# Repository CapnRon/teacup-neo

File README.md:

# Teacup Neo

T41 (QFN96) adaptation of the [Teacup Rev-C](https://github.com/CapnRon/Teacup) T31 development board.

Targets **T41NQ (128MB)**, **T41XQ (256MB)**, and **T41LQ (64MB)** — all three are
pin-identical in the QFN96 package, so one layout serves all three as a stuffing
option (LQ needs the DDR rail set to 1.8V instead of 1.35V via the FB divider).

> **Where this is going:** teacup-neo is the single-SoC (T41) proof for a modular
> platform — a universal baseboard + per-SoC MXM3 interposer modules that host any
> Ingenic T-series/A1 SoC regardless of package. Full spec in
> [`docs/UNIVERSAL.md`](docs/UNIVERSAL.md).

## Status

| Stage | State |
|-------|-------|
| Pin map / power design | complete, verified against 3 datasheets |
| QFN96 footprint + T41NQ symbol | KiCad-validated |
| Schematic | **netlist-verified** — all 97 SoC pins on intended nets, 0 peripheral connections lost |
| PCB netlist applied | 479 pads re-netted, 0 mismatch |
| Routing | **~83% auto-routed** (FreeRouting); 78 nets + placement + 3 shorts need GUI finishing |
| Manufacturing outputs | BOM/pos complete; Gerbers are a **draft** (board not yet fab-ready) |

**This board is NOT fab-ready.** The design (schematic + netlist) is complete and
fully verified, but the PCB was auto-routed headlessly with best-effort blind
placement. Before fabrication it needs, in the KiCad GUI:
- placement de-overlap of the bottom-side power section (7 courtyard overlaps)
- the 78 remaining ratsnest connections routed
- 3 shorts / clearance violations resolved
- **MIPI CSI routed as 100 ohm impedance-controlled differential pairs** (an
  autorouter does not do controlled impedance)
- SFC/DDR length + return-path review per the T41 Hardware Design Guide

## Power tree

2x SY8089A1AAC buck (core 0.8V/2A EN<-1.35V, DDR 1.35V EN<-1.8V) + kept AZ1117
LDOs (3.3V, 1.8V). EN cascade gives the datasheet power-on order. See `docs/POWER.md`.

## Layout

- `hw/` — KiCad project (based on TeaCup(C)3.3)
- `hw/Manufacturing/` — draft Gerbers, drill, BOM, position, DRC report
- `docs/` — pin maps, power design, netlist verification
- `scripts/` — the headless generators (footprint, symbol, schematic, PCB, routing)
- `reference/` — upstream 3.3 artifacts

Built headlessly with KiCad 9.0.2 (kicad-cli + pcbnew) + FreeRouting 1.9.0.

License: GPL-3.0 (inherited from upstream).

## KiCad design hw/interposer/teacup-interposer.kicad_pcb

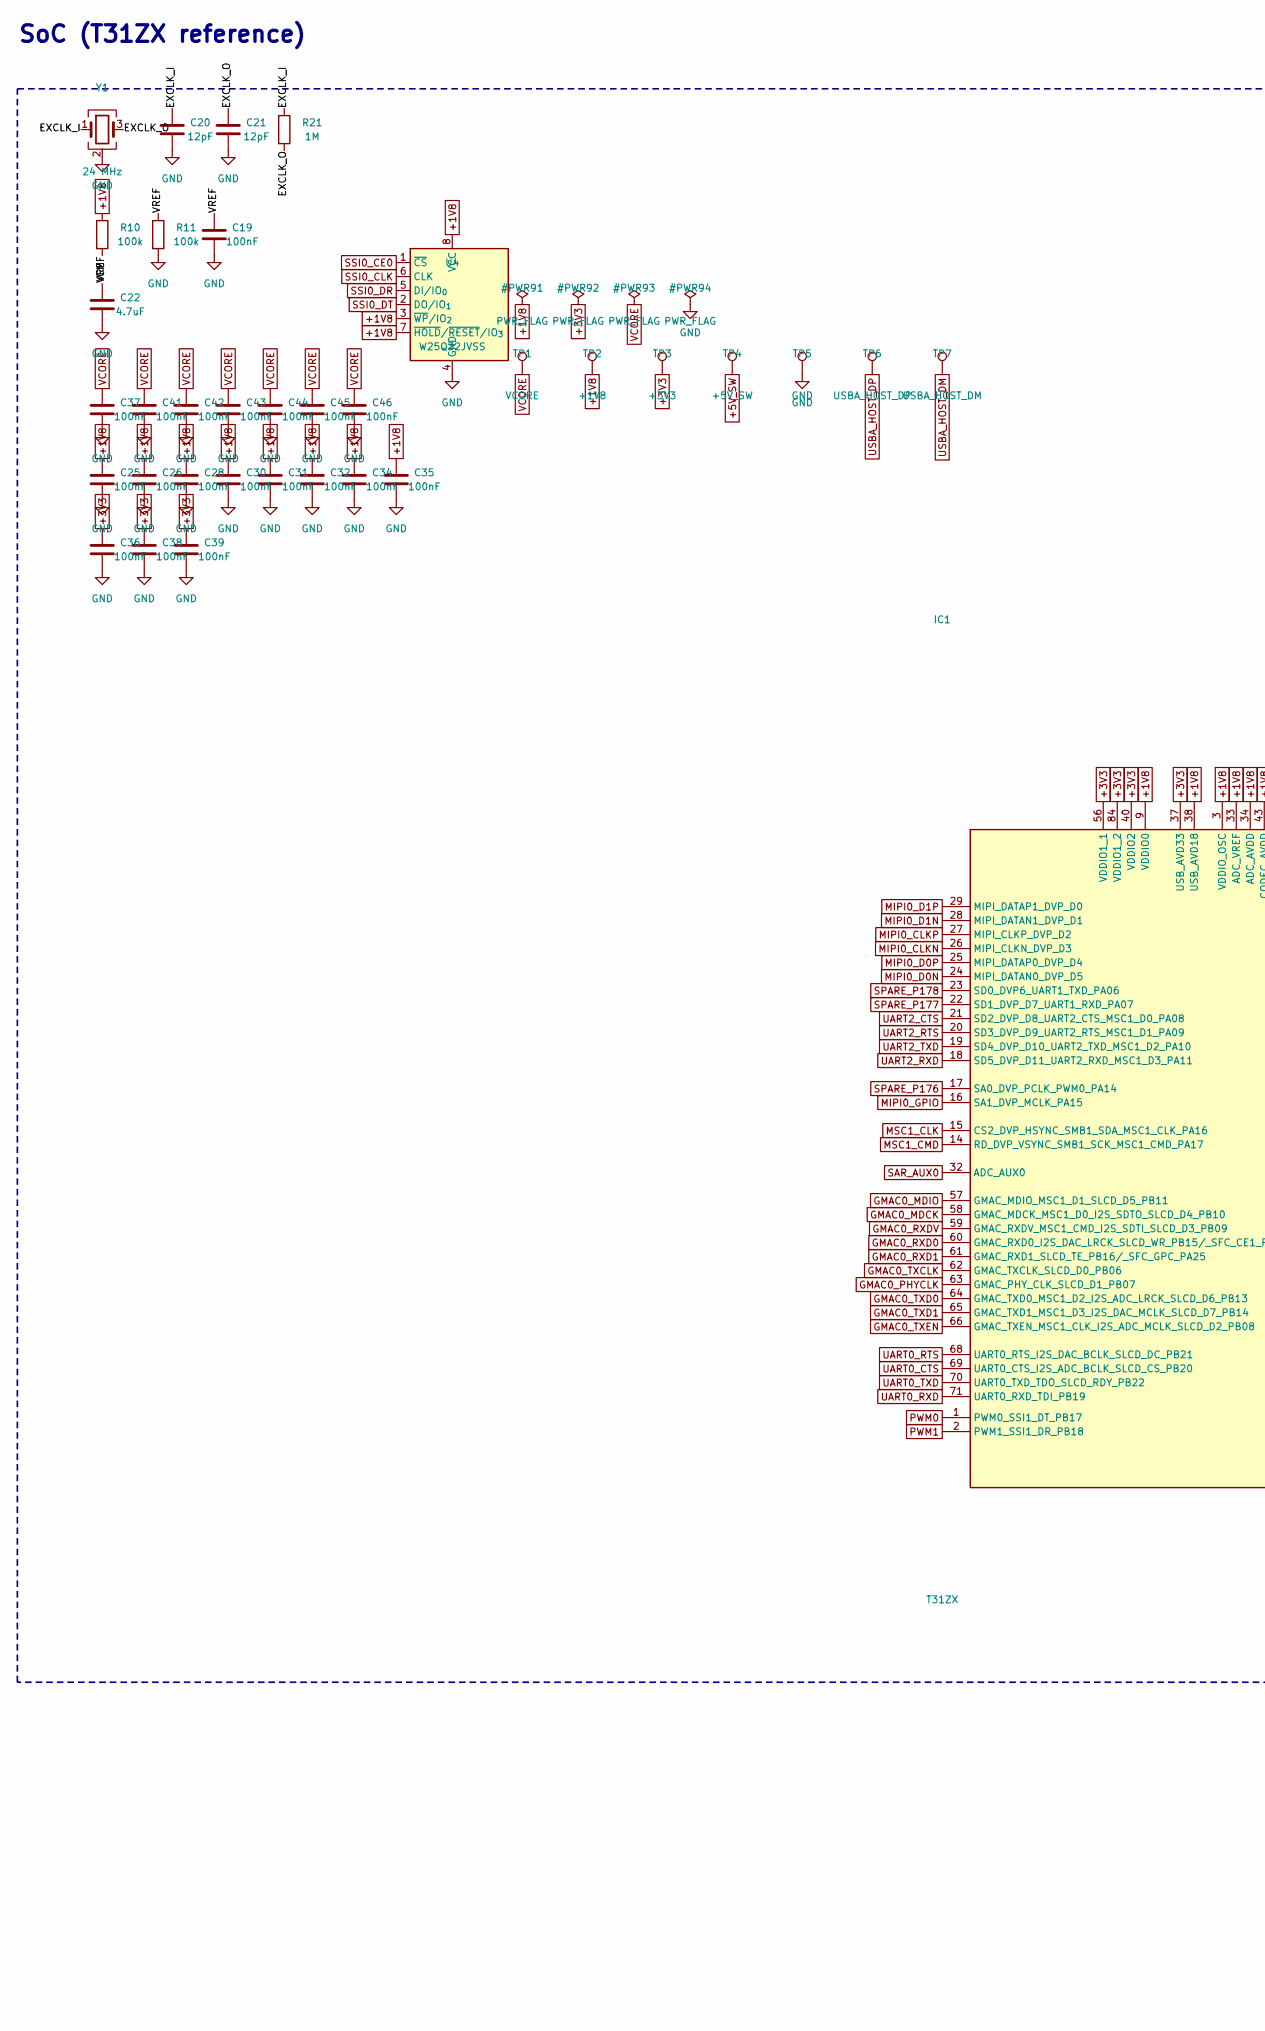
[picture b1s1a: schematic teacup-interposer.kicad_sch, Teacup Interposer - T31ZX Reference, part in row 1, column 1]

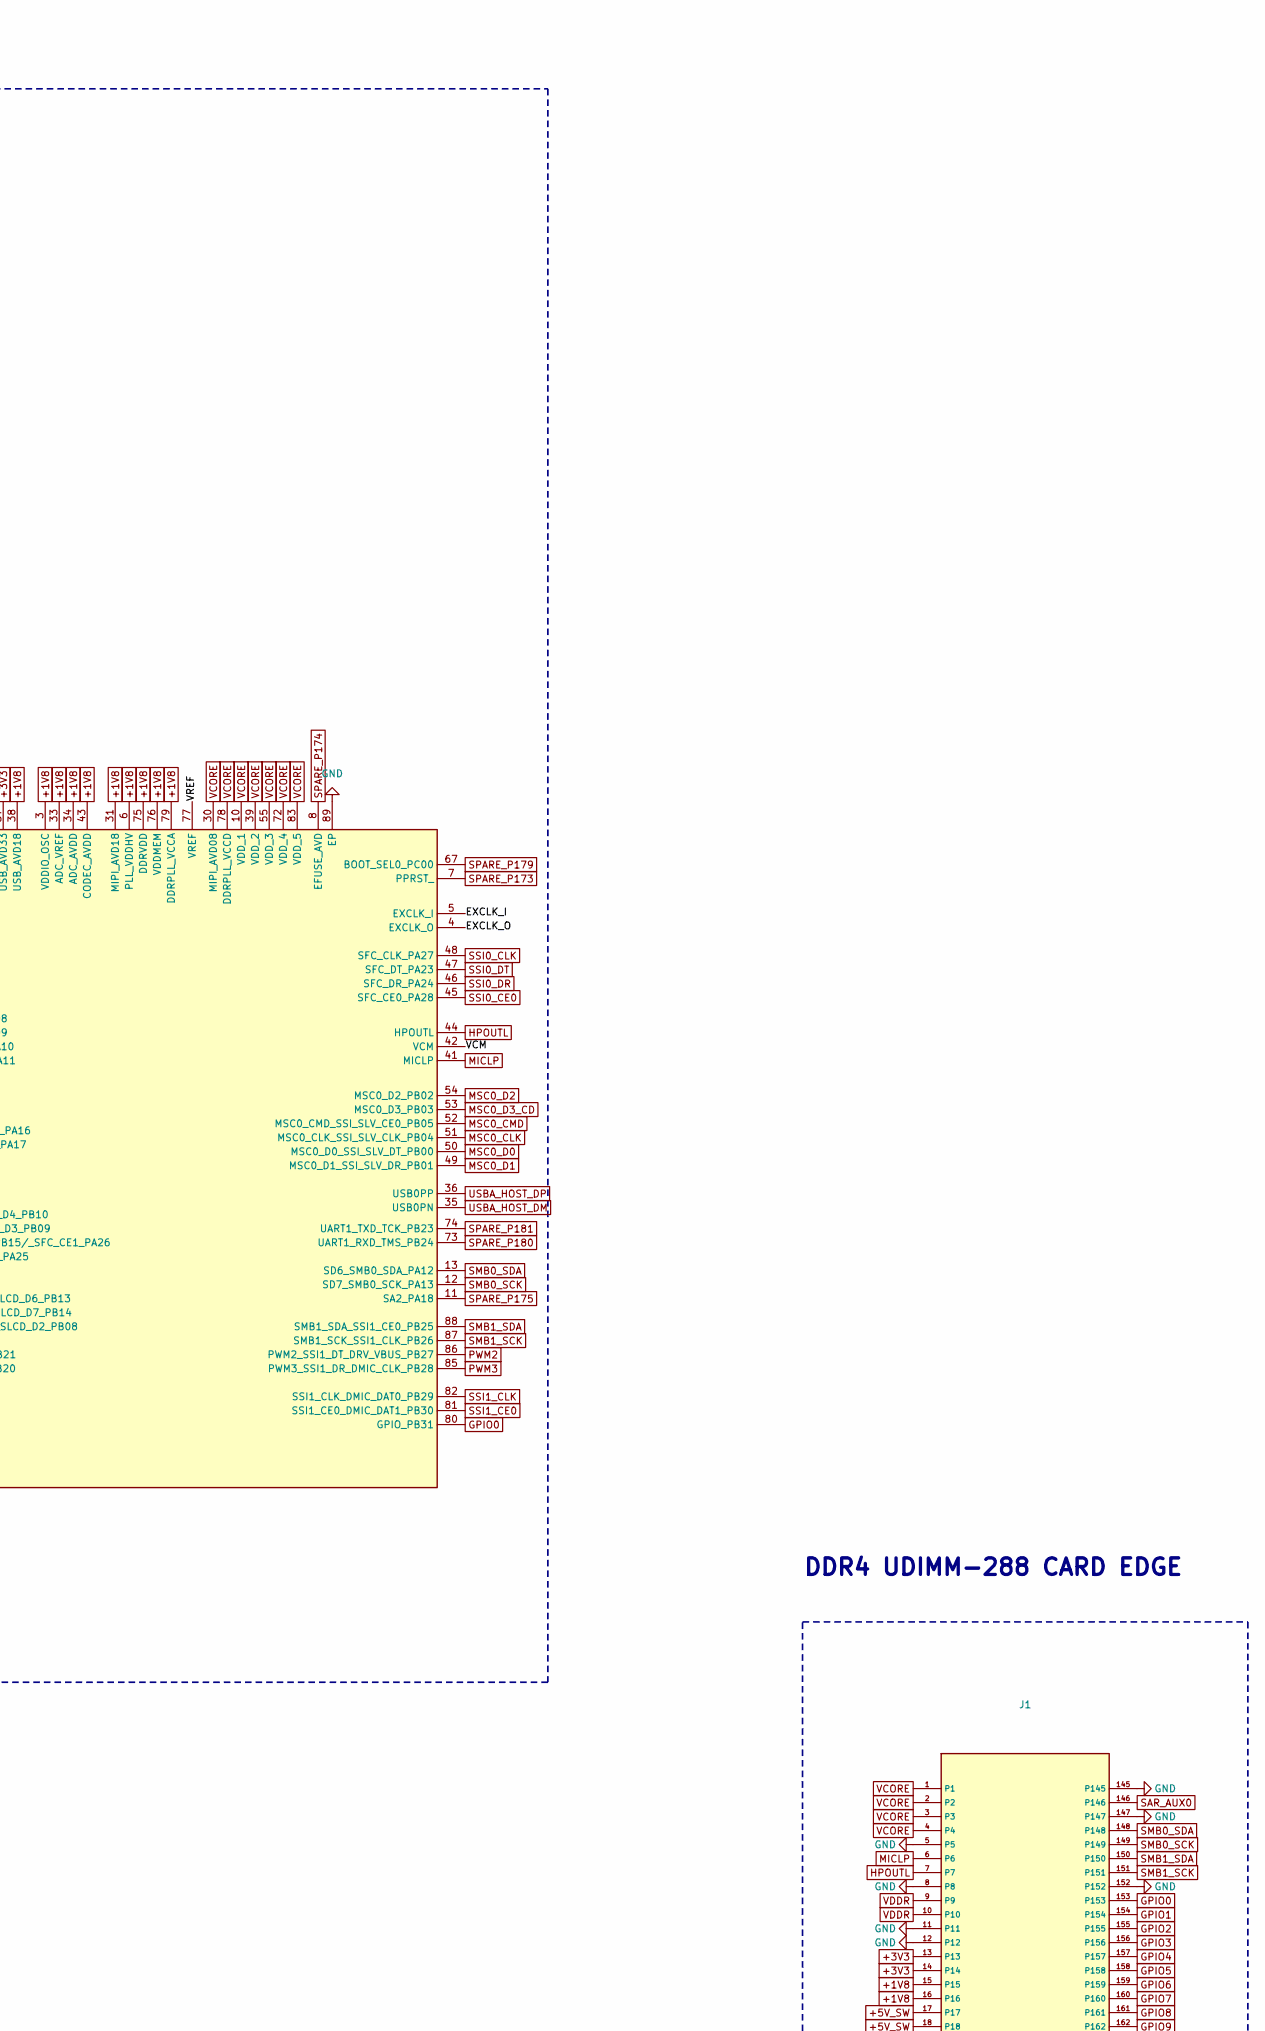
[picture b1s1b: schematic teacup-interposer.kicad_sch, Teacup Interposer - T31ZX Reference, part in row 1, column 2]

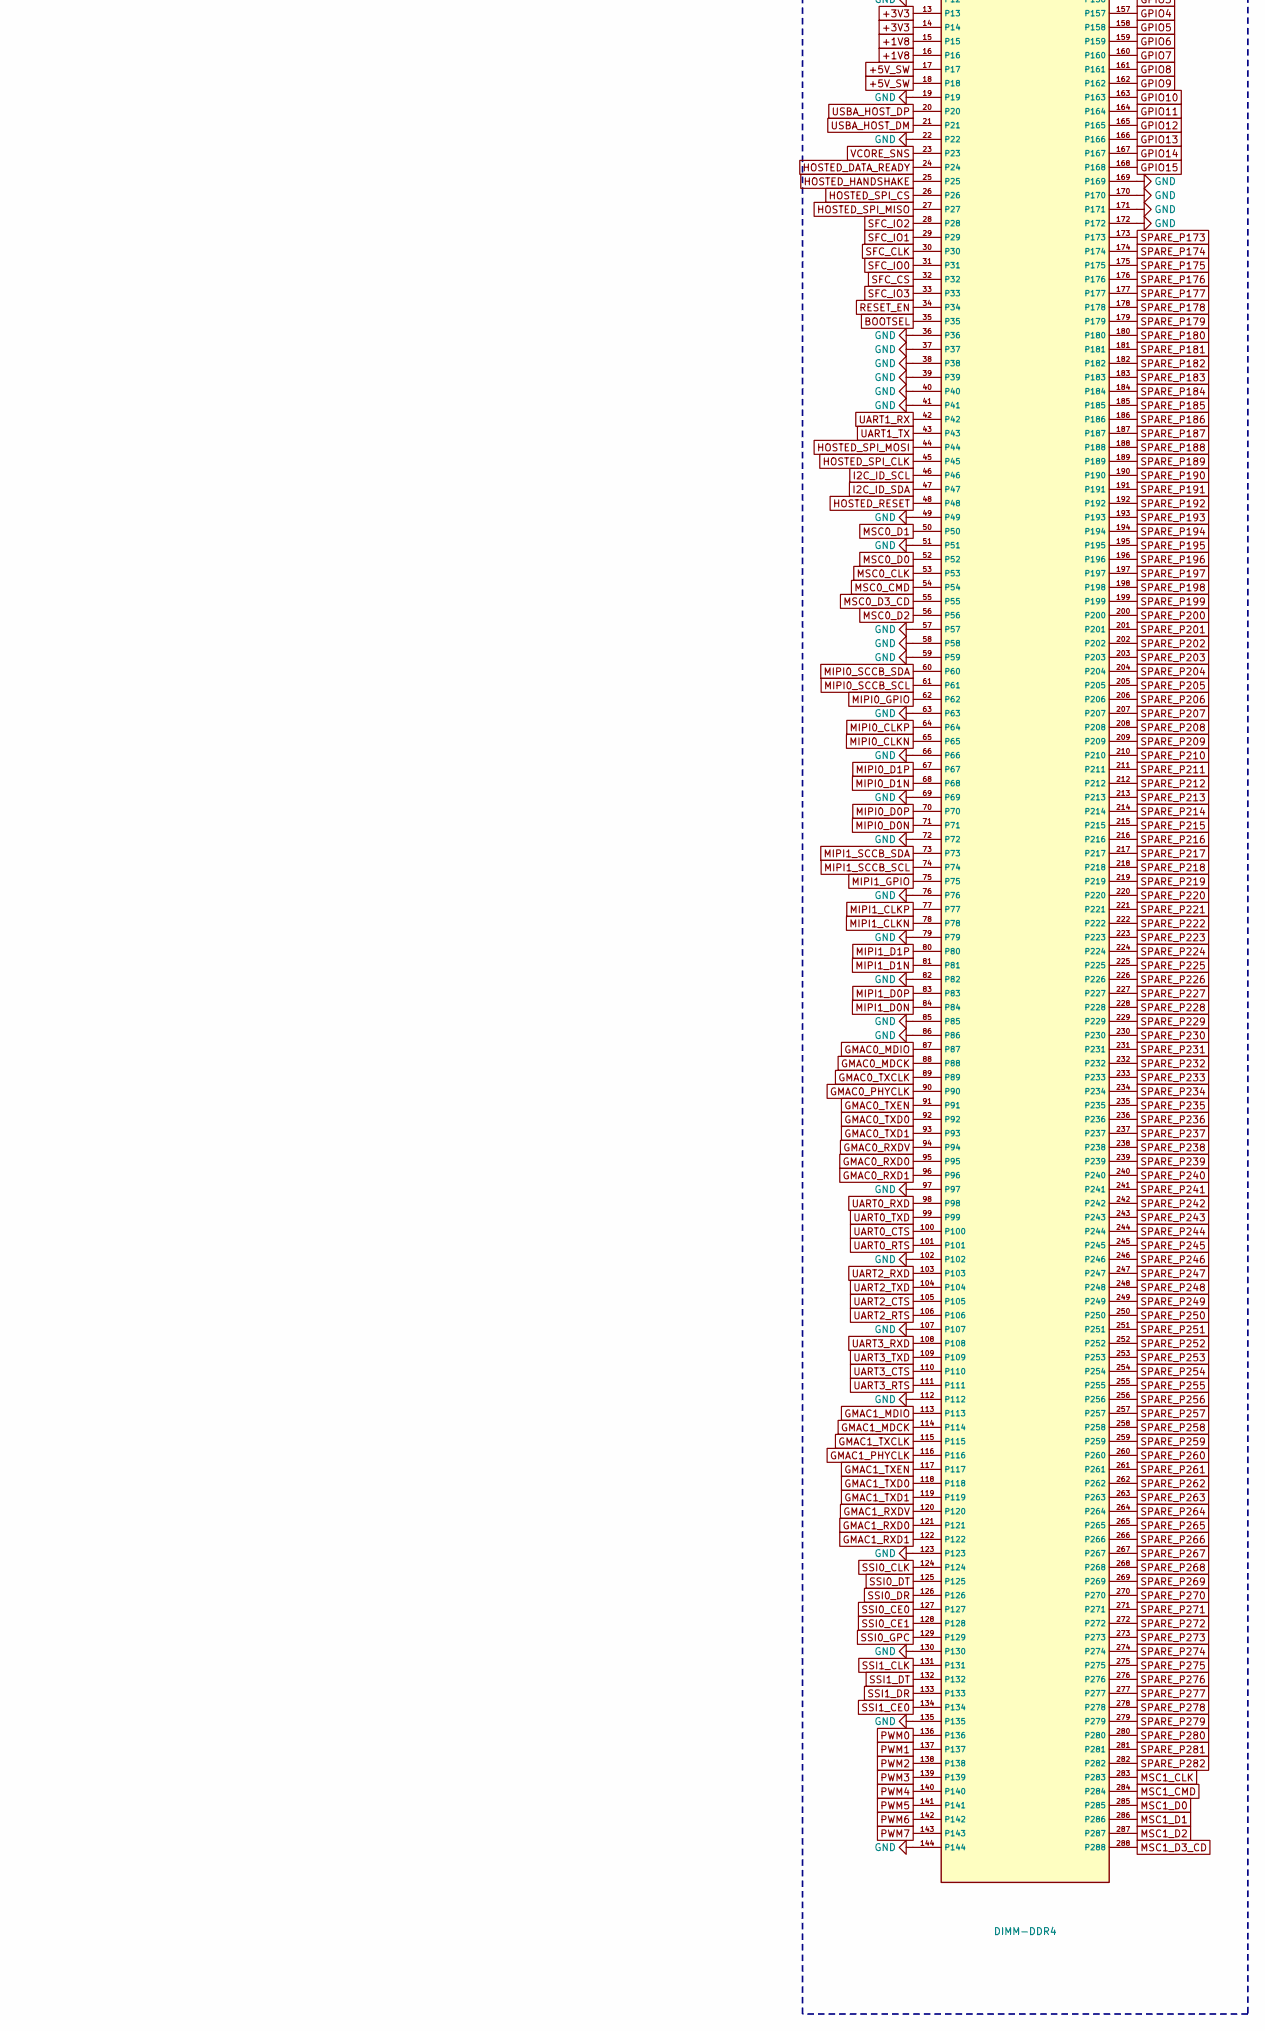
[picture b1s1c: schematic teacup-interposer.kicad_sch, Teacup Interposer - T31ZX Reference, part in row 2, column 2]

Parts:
C19: 100nF; C_0603_1608Metric
C20, C21: 12pF; C_0402_1005Metric
C22: 4.7uF; C_0603_1608Metric_Pad1.08x0.95mm_HandSolder
C25, C26, C28, C30, C31, C32, C34, C35, C36, C37, C38, C39, C41, C42, C43, C44, C45, C46: 100nF; C_0402_1005Metric
IC1: T31ZX; QFN35P900X900X90-89N-D; MPN T31ZX
J1: DIMM-DDR4
R10, R11: 100k; R_0603_1608Metric
R21: 1M; R_0402_1005Metric
TP1: VCORE; TestPoint_Pad_2.0x2.0mm
TP2: +1V8; TestPoint_Pad_2.0x2.0mm
TP3: +3V3; TestPoint_Pad_2.0x2.0mm
TP4: +5V_SW; TestPoint_Pad_2.0x2.0mm
TP5: GND; TestPoint_Pad_2.0x2.0mm
TP6: USBA_HOST_DP; TestPoint_Pad_2.0x2.0mm
TP7: USBA_HOST_DM; TestPoint_Pad_2.0x2.0mm
U4: W25Q32JVSS; SOIC-8_5.3x5.3mm_P1.27mm; MPN W25Q32JVSS
Y1: 24 MHz; Crystal_SMD_2016-4Pin_2.0x1.6mm

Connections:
+5V_SW: J1.17, J1.18, TP4.1
/EXCLK_O: C21.1, IC1.4 (EXCLK_O), R21.2, Y1.3
/VCM: C22.1, IC1.42 (VCM)
/VREF: C19.1, IC1.77 (VREF), R10.2, R11.1
BOOTSEL: J1.35
GMAC0_MDCK: IC1.58 (GMAC_MDCK_MSC1_D0_I2S_SDTO_SLCD_D4_PB10), J1.88
GMAC0_MDIO: IC1.57 (GMAC_MDIO_MSC1_D1_SLCD_D5_PB11), J1.87
GMAC0_PHYCLK: IC1.63 (GMAC_PHY_CLK_SLCD_D1_PB07), J1.90
GMAC0_RXD0: IC1.60 (GMAC_RXD0_I2S_DAC_LRCK_SLCD_WR_PB15/_SF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), J1.95
GMAC0_RXD1: IC1.61 (GMAC_RXD1_SLCD_TE_PB16/_SFC_GPC_PA25), J1.96
GMAC0_RXDV: IC1.59 (GMAC_RXDV_MSC1_CMD_I2S_SDTI_SLCD_D3_PB09), J1.94
GMAC0_TXCLK: IC1.62 (GMAC_TXCLK_SLCD_D0_PB06), J1.89
GMAC0_TXD0: IC1.64 (GMAC_TXD0_MSC1_D2_I2S_ADC_LRCK_SLCD_D6_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), J1.92
GMAC0_TXD1: IC1.65 (GMAC_TXD1_MSC1_D3_I2S_DAC_MCLK_SLCD_D7_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), J1.93
GMAC0_TXEN: IC1.66 (GMAC_TXEN_MSC1_CLK_I2S_ADC_MCLK_SLCD_D2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), J1.91
GMAC1_MDCK: J1.114
GMAC1_MDIO: J1.113
GMAC1_PHYCLK: J1.116
GMAC1_RXD0: J1.121
GMAC1_RXD1: J1.122
GMAC1_RXDV: J1.120
GMAC1_TXCLK: J1.115
GMAC1_TXD0: J1.118
GMAC1_TXD1: J1.119
GMAC1_TXEN: J1.117
GPIO0: IC1.80 (GPIO_PB31), J1.153
GPIO1: J1.154
GPIO2: J1.155
GPIO3: J1.156
GPIO4: J1.157
GPIO5: J1.158
GPIO6: J1.159
GPIO7: J1.160
GPIO8: J1.161
GPIO9: J1.162
GPIO10: J1.163
GPIO11: J1.164
GPIO12: J1.165
GPIO13: J1.166
GPIO14: J1.167
GPIO15: J1.168
HOSTED_DATA_READY: J1.24
HOSTED_HANDSHAKE: J1.25
HOSTED_RESET: J1.48
HOSTED_SPI_CLK: J1.45
HOSTED_SPI_CS: J1.26
HOSTED_SPI_MISO: J1.27
HOSTED_SPI_MOSI: J1.44
HPOUTL: IC1.44 (HPOUTL), J1.7
I2C_ID_SCL: J1.46
I2C_ID_SDA: J1.47
MICLP: IC1.41 (MICLP), J1.6
MIPI0_CLKN: IC1.26 (MIPI_CLKN_DVP_D3), J1.65
MIPI0_CLKP: IC1.27 (MIPI_CLKP_DVP_D2), J1.64
MIPI0_D0N: IC1.24 (MIPI_DATAN0_DVP_D5), J1.71
MIPI0_D0P: IC1.25 (MIPI_DATAP0_DVP_D4), J1.70
MIPI0_D1N: IC1.28 (MIPI_DATAN1_DVP_D1), J1.68
MIPI0_D1P: IC1.29 (MIPI_DATAP1_DVP_D0), J1.67
MIPI0_GPIO: IC1.16 (SA1_DVP_MCLK_PA15), J1.62
MIPI0_SCCB_SCL: J1.61
MIPI0_SCCB_SDA: J1.60
MIPI1_CLKN: J1.78
MIPI1_CLKP: J1.77
MIPI1_D0N: J1.84
MIPI1_D0P: J1.83
MIPI1_D1N: J1.81
MIPI1_D1P: J1.80
MIPI1_GPIO: J1.75
MIPI1_SCCB_SCL: J1.74
MIPI1_SCCB_SDA: J1.73
MSC0_CLK: IC1.51 (MSC0_CLK_SSI_SLV_CLK_PB04), J1.53
MSC0_CMD: IC1.52 (MSC0_CMD_SSI_SLV_CE0_PB05), J1.54
MSC0_D0: IC1.50 (MSC0_D0_SSI_SLV_DT_PB00), J1.52
MSC0_D1: IC1.49 (MSC0_D1_SSI_SLV_DR_PB01), J1.50
MSC0_D2: IC1.54 (MSC0_D2_PB02), J1.56
MSC0_D3_CD: IC1.53 (MSC0_D3_PB03), J1.55
MSC1_CLK: IC1.15 (CS2_DVP_HSYNC_SMB1_SDA_MSC1_CLK_PA16), J1.283
MSC1_CMD: IC1.14 (RD_DVP_VSYNC_SMB1_SCK_MSC1_CMD_PA17), J1.284
MSC1_D0: J1.285
MSC1_D1: J1.286
MSC1_D2: J1.287
MSC1_D3_CD: J1.288
PWM0: IC1.1 (PWM0_SSI1_DT_PB17), J1.136
PWM1: IC1.2 (PWM1_SSI1_DR_PB18), J1.137
PWM2: IC1.86 (PWM2_SSI1_DT_DRV_VBUS_PB27), J1.138
PWM3: IC1.85 (PWM3_SSI1_DR_DMIC_CLK_PB28), J1.139
PWM4: J1.140
PWM5: J1.141
PWM6: J1.142
PWM7: J1.143
RESET_EN: J1.34
SAR_AUX0: IC1.32 (ADC_AUX0), J1.146
SFC_CLK: J1.30
SFC_CS: J1.32
SFC_IO0: J1.31
SFC_IO1: J1.29
SFC_IO2: J1.28
SFC_IO3: J1.33
SMB0_SCK: IC1.12 (SD7_SMB0_SCK_PA13), J1.149
SMB0_SDA: IC1.13 (SD6_SMB0_SDA_PA12), J1.148
SMB1_SCK: IC1.87 (SMB1_SCK_SSI1_CLK_PB26), J1.151
SMB1_SDA: IC1.88 (SMB1_SDA_SSI1_CE0_PB25), J1.150
SPARE_P173: IC1.7 (PPRST_), J1.173
SPARE_P174: IC1.8 (EFUSE_AVD), J1.174
SPARE_P175: IC1.11 (SA2_PA18), J1.175
SPARE_P176: IC1.17 (SA0_DVP_PCLK_PWM0_PA14), J1.176
SPARE_P177: IC1.22 (SD1_DVP_D7_UART1_RXD_PA07), J1.177
SPARE_P178: IC1.23 (SD0_DVP6_UART1_TXD_PA06), J1.178
SPARE_P179: IC1.67 (BOOT_SEL0_PC00), J1.179
SPARE_P180: IC1.73 (UART1_RXD_TMS_PB24), J1.180
SPARE_P181: IC1.74 (UART1_TXD_TCK_PB23), J1.181
SPARE_P182: J1.182
SPARE_P183: J1.183
SPARE_P184: J1.184
SPARE_P185: J1.185
SPARE_P186: J1.186
SPARE_P187: J1.187
SPARE_P188: J1.188
SPARE_P189: J1.189
SPARE_P190: J1.190
SPARE_P191: J1.191
SPARE_P192: J1.192
SPARE_P193: J1.193
SPARE_P194: J1.194
SPARE_P195: J1.195
SPARE_P196: J1.196
SPARE_P197: J1.197
SPARE_P198: J1.198
SPARE_P199: J1.199
SPARE_P200: J1.200
SPARE_P201: J1.201
SPARE_P202: J1.202
SPARE_P203: J1.203
SPARE_P204: J1.204
SPARE_P205: J1.205
SPARE_P206: J1.206
SPARE_P207: J1.207
SPARE_P208: J1.208
SPARE_P209: J1.209
SPARE_P210: J1.210
SPARE_P211: J1.211
SPARE_P212: J1.212
SPARE_P213: J1.213
SPARE_P214: J1.214
SPARE_P215: J1.215
SPARE_P216: J1.216
SPARE_P217: J1.217
SPARE_P218: J1.218
SPARE_P219: J1.219
SPARE_P220: J1.220
SPARE_P221: J1.221
SPARE_P222: J1.222
SPARE_P223: J1.223
SPARE_P224: J1.224
SPARE_P225: J1.225
SPARE_P226: J1.226
SPARE_P227: J1.227
SPARE_P228: J1.228
SPARE_P229: J1.229
SPARE_P230: J1.230
SPARE_P231: J1.231
SPARE_P232: J1.232
SPARE_P233: J1.233
SPARE_P234: J1.234
SPARE_P235: J1.235
SPARE_P236: J1.236
SPARE_P237: J1.237
SPARE_P238: J1.238
SPARE_P239: J1.239
SPARE_P240: J1.240
SPARE_P241: J1.241
SPARE_P242: J1.242
SPARE_P243: J1.243
SPARE_P244: J1.244
SPARE_P245: J1.245
SPARE_P246: J1.246
SPARE_P247: J1.247
SPARE_P248: J1.248
SPARE_P249: J1.249
SPARE_P250: J1.250
SPARE_P251: J1.251
SPARE_P252: J1.252
SPARE_P253: J1.253
SPARE_P254: J1.254
SPARE_P255: J1.255
SPARE_P256: J1.256
SPARE_P257: J1.257
SPARE_P258: J1.258
SPARE_P259: J1.259
SPARE_P260: J1.260
SPARE_P261: J1.261
SPARE_P262: J1.262
SPARE_P263: J1.263
SPARE_P264: J1.264
SPARE_P265: J1.265
SPARE_P266: J1.266
SPARE_P267: J1.267
SPARE_P268: J1.268
SPARE_P269: J1.269
SPARE_P270: J1.270
SPARE_P271: J1.271
SPARE_P272: J1.272
SPARE_P273: J1.273
SPARE_P274: J1.274
SPARE_P275: J1.275
SPARE_P276: J1.276
SPARE_P277: J1.277
SPARE_P278: J1.278
SPARE_P279: J1.279
SPARE_P280: J1.280
SPARE_P281: J1.281
SPARE_P282: J1.282
SSI0_CE0: IC1.45 (SFC_CE0_PA28), J1.127, U4.1 (~CS)
SSI0_CE1: J1.128
SSI0_CLK: IC1.48 (SFC_CLK_PA27), J1.124, U4.6 (CLK)
SSI0_DR: IC1.46 (SFC_DR_PA24), J1.126, U4.5 (DI/IO_{0})
SSI0_DT: IC1.47 (SFC_DT_PA23), J1.125, U4.2 (DO/IO_{1})
SSI0_GPC: J1.129
SSI1_CE0: IC1.81 (SSI1_CE0_DMIC_DAT1_PB30), J1.134
SSI1_CLK: IC1.82 (SSI1_CLK_DMIC_DAT0_PB29), J1.131
SSI1_DR: J1.133
SSI1_DT: J1.132
UART0_CTS: IC1.69 (UART0_CTS_I2S_ADC_BCLK_SLCD_CS_PB20), J1.100
UART0_RTS: IC1.68 (UART0_RTS_I2S_DAC_BCLK_SLCD_DC_PB21), J1.101
UART0_RXD: IC1.71 (UART0_RXD_TDI_PB19), J1.98
UART0_TXD: IC1.70 (UART0_TXD_TDO_SLCD_RDY_PB22), J1.99
UART1_RX: J1.42
UART1_TX: J1.43
UART2_CTS: IC1.21 (SD2_DVP_D8_UART2_CTS_MSC1_D0_PA08), J1.105
UART2_RTS: IC1.20 (SD3_DVP_D9_UART2_RTS_MSC1_D1_PA09), J1.106
UART2_RXD: IC1.18 (SD5_DVP_D11_UART2_RXD_MSC1_D3_PA11), J1.103
UART2_TXD: IC1.19 (SD4_DVP_D10_UART2_TXD_MSC1_D2_PA10), J1.104
UART3_CTS: J1.110
UART3_RTS: J1.111
UART3_RXD: J1.108
UART3_TXD: J1.109
USBA_HOST_DM: IC1.35 (USB0PN), J1.21, TP7.1
USBA_HOST_DP: IC1.36 (USB0PP), J1.20, TP6.1
VCORE_SNS: J1.23
VDDR: J1.9, J1.10

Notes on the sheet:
SoC (T31ZX reference)
DDR4 UDIMM-288 CARD EDGE

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
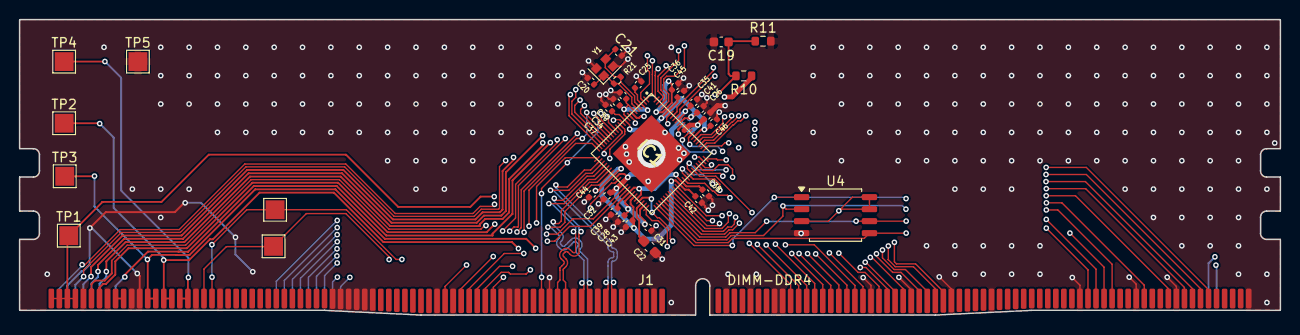
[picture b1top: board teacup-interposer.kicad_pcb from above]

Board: 4 copper layers, 133.3 x 31.2 mm, 36 parts (0 on the bottom side), 72 nets.

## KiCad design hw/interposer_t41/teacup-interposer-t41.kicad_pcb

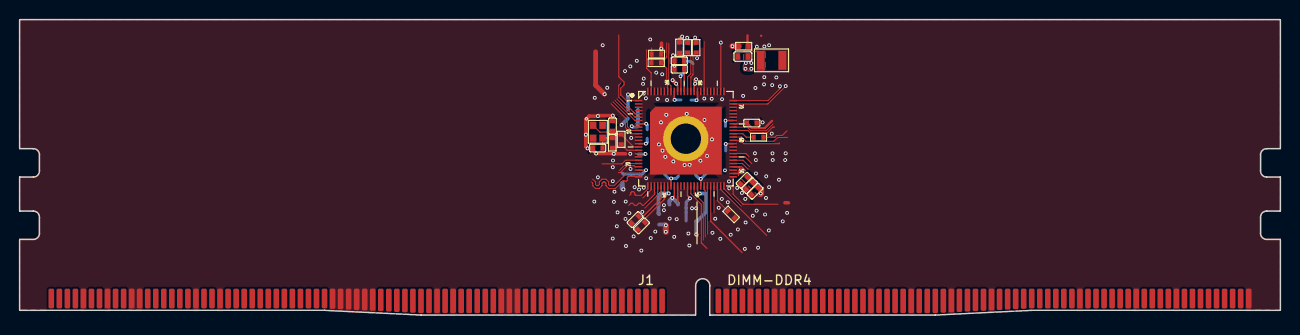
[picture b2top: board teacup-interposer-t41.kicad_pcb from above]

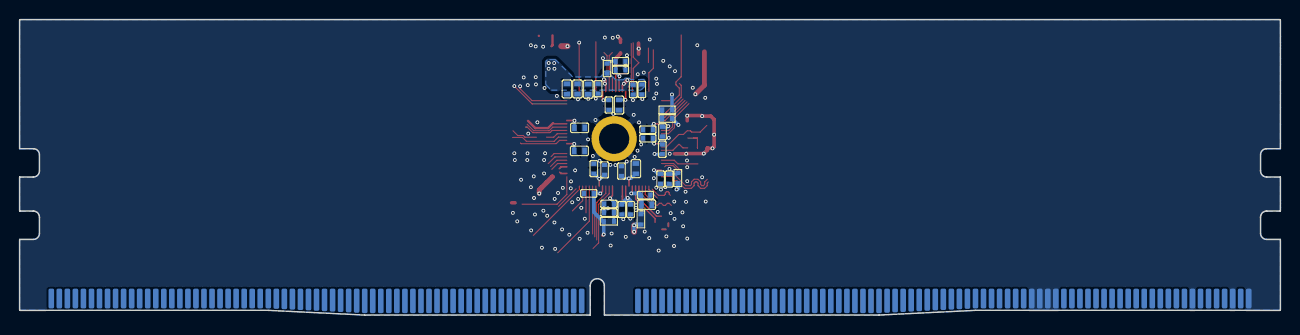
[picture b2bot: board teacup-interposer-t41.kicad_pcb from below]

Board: 4 copper layers, 133.4 x 31.2 mm, 61 parts (35 on the bottom side), 82 nets.

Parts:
J1: DIMM-DDR4
RT1, RT2, RT3, RT4, RT5, RT6, RT7, RT8, RT9, RT10, RT11, RT12, RT13, RT14, RT15, RT16, RT17, RT18, RT19, RT20, RT21, RT22, RT23, RT24, RT25, RT26, RT27, RT28, RT29, RT30, RT31, RT32, RT33, RT34, RT35, RT36, RT37, RT38, RT39, RT40, RT41, RT42, RT43, RT44, RT45, RT46, RT47, RT48, RT49, RT50, RT51, RT52, RT53, RT54, RT55, RT56, RT57, RT58: ?
U11: T41
Y1: 24MHz

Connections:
+1V8: J1.15, J1.16, RT5.1, RT5.2, RT6.1, RT8.2, RT11.1, RT12.1, RT16.1, RT17.1, RT19.2, RT21.1, RT21.2, RT27.1, RT28.1, RT29.1, RT29.2, RT51.1, RT52.1, RT53.2, RT55.2, U11.17, U11.22, U11.31, U11.50, U11.52, U11.85
+3V3: J1.13, J1.14, RT7.1, RT7.2, RT8.1, RT10.1, RT34.1, RT36.1, RT37.1, RT37.2, RT43.1, RT54.1, U11.9, U11.37, U11.40, U11.65
+5V_SW: J1.17, J1.18
DDR_VREF: RT30.2, RT31.2, RT38.1, U11.86
DDR_ZQ: RT40.1, U11.83
EXCLK_I: RT3.2, RT4.2, U11.15, Y1.1
EXCLK_O: RT2.2, RT4.1, U11.16
EXCLK_O_INT: RT2.1, RT58.2, Y1.3
GMAC0_MDCK: J1.88, U11.49
GMAC0_MDIO: J1.87, U11.48
GMAC0_PHYCLK: J1.90, RT48.1, RT48.2, U11.46
GMAC0_RXD0: J1.95, U11.58
GMAC0_RXD1: J1.96, U11.57
GMAC0_RXDV: J1.94, U11.47
GMAC0_TXCLK: J1.89, U11.56
GMAC0_TXD0: J1.92, U11.55
GMAC0_TXD1: J1.93, U11.54
GMAC0_TXEN: J1.91, U11.53
GND: J1.5, J1.8, J1.11, J1.12, J1.19, J1.22, J1.36, J1.37, J1.38, J1.39, J1.40, J1.41, J1.49, J1.51, J1.57, J1.58, J1.59, J1.63, J1.66, J1.69, J1.72, J1.76, J1.79, J1.82, J1.85, J1.86, J1.97, J1.102, J1.107, J1.112, J1.123, J1.130, J1.135, J1.144, J1.145, J1.147, J1.152, J1.169, J1.170, J1.171, J1.172, RT1.1, RT3.1, RT6.2, RT10.2, RT11.2, RT12.2, RT14.2, RT15.2, RT16.2, RT17.2, RT20.2, RT22.2, RT23.2, RT24.1, RT25.1, RT26.2, RT27.2, RT28.2, RT30.1, RT31.1, RT32.2, RT33.2, RT34.2, RT35.2, RT36.2, RT39.2, RT40.2, RT41.2, RT42.2, RT43.2, RT44.2, RT45.2, RT46.2, RT47.2, RT49.2, RT50.2, RT52.2, RT53.1, RT54.2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
GPIO0: J1.153, U11.79
HPOUTL: J1.7, U11.34
MICLP: J1.6, RT9.1, U11.29
MIPI0_CLKN: J1.65, U11.26
MIPI0_CLKP: J1.64, U11.25
MIPI0_D0N: J1.71, U11.24
MIPI0_D0P: J1.70, U11.23
MIPI0_D1N: J1.68, U11.28
MIPI0_D1P: J1.67, U11.27
MIPI0_GPIO: J1.62, U11.19
MSC0_CLK: J1.53, RT56.1, RT56.2, U11.62
MSC0_CMD: J1.54, U11.68
MSC0_D0: J1.52, U11.63
MSC0_D1: J1.50, U11.61
MSC0_D2: J1.56, U11.67
MSC0_D3_CD: J1.55, U11.64
MSC1_CLK: J1.283, U11.11
MSC1_CMD: J1.284, U11.10
MSC1_D0: J1.285, U11.7
MSC1_D1: J1.286, U11.6
MSC1_D2: J1.287, U11.13
MSC1_D3_CD: J1.288, U11.12
PWM0: J1.136, U11.72
PWM1: J1.137, U11.71
RZQ: RT33.1, U11.84
SAR_AUX0: J1.146, U11.51
SMB0_SCK: J1.149, U11.21
SMB0_SDA: J1.148, U11.20
SMB1_SCK: J1.151, U11.78
SMB1_SDA: J1.150, U11.77
SPARE_P175: J1.175, U11.18
SPARE_P179: J1.179, U11.80
SPARE_P182: J1.182, RT13.1, U11.30
SPARE_P183: J1.183, U11.42
SPARE_P184: J1.184, U11.45
SPARE_P185: J1.185, U11.69
SPARE_P186: J1.186, U11.70
SPARE_P187: J1.187, U11.73
SPARE_P188: J1.188, U11.74
SPARE_P189: J1.189, U11.75
SPARE_P190: J1.190, U11.76
SPARE_P191: J1.191, U11.93
SSI0_CE0: J1.127, U11.38
SSI0_CLK: J1.124, U11.44
SSI0_DR: J1.126, U11.39
SSI0_DT: J1.125, U11.43
SSI1_CE0: J1.134, U11.4
SSI1_CLK: J1.131, U11.3
SSI1_DR: J1.133, U11.1
SSI1_DT: J1.132, U11.5
UART0_CTS: J1.100, U11.2
UART0_RTS: J1.101, U11.96
UART0_RXD: J1.98, U11.94
UART0_TXD: J1.99, U11.95
UART2_CTS: J1.105, U11.89
UART2_RTS: J1.106, RT18.1, RT18.2, RT19.1, U11.90
UART2_RXD: J1.103, U11.91
UART2_TXD: J1.104, U11.92
USBA_HOST_DM: J1.21, U11.35
USBA_HOST_DP: J1.20, U11.36
VCM: RT24.2, RT25.2, U11.33
VCORE: J1.1, J1.2, J1.3, J1.4, RT14.1, RT15.1, RT22.1, RT26.1, RT32.1, RT35.1, RT39.1, RT42.1, RT45.1, RT46.1, U11.8, U11.14, U11.32, U11.41, U11.59, U11.66, U11.81, U11.88
VDDR: J1.9, J1.10, RT20.1, RT23.1, RT38.2, RT41.1, RT44.1, RT47.1, RT49.1, RT50.1, RT51.2, RT57.1, RT57.2, U11.82, U11.87

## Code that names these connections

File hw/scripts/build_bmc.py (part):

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    12: "BOOTSEL",
    13: "BMC_USB_DM", 14: "BMC_USB_DP",   # now via dedicated J9, not J2
    15: "RESET_EN",
    16: "SW5V_EN_ALT",               # GPIO select: alt-branch load switch (U14) -- native, margin testing
    17: "SFC_IO3", 18: "SFC_CS", 19: "SFC_IO0",
    20: "SFC_CLK", 21: "SFC_IO1", 22: "SFC_IO2",
    23: "HOSTED_SPI_MISO", 24: "HOSTED_SPI_CS",    # ESP-Hosted full-duplex SPI to interposer
    25: "HOSTED_HANDSHAKE",          # ESP-Hosted: co-processor -> host, data-ready-to-send
    26: "HOSTED_DATA_READY",         # ESP-Hosted: co-processor -> host, packet pending
    27: "U8_BOOT",                  # GPIO0/BOOT strap, R9 pull-up
    28: "EXP_INT",                   # U15 (TCA9555) interrupt, active low
    29: None, 35: None,              # spare
    30: "EN_CS_U4", 31: "EN_CS_U5",  # native, margin testing
    32: "USB_OC1", 33: "USB_OC2", 34: "USB_OC3",   # native -- fast overcurrent response
    36: "ESP32_CONSOLE_RX", 37: "ESP32_CONSOLE_TX",
    38: "SW5V_EN_BMC", 39: "VCORE_SNS",   # GPIO select: BMC-branch load switch (U4) -- native, margin testing
}
for num, spec in U8_PINS.items():
    ic_pin(U8, u8x, u8y, num, spec)
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    s.place(TS, ref, "TS5A3166", tx, y, 0, footprint="Package_TO_SOT_SMD:SOT-23-5",
            ref_at=(tx, y - S(6), 0), value_at=(tx, y + S(6), 0))
    ic_pin(TS, tx, y, 1, no_net)      # NO
    ic_pin(TS, tx, y, 2, "SFC_CS")    # COM
    ic_pin(TS, tx, y, 3, GNDF)        # GND
    ic_pin(TS, tx, y, 4, in_net)      # IN
    ic_pin(TS, tx, y, 5, P3V3F)       # V+
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s.place(SW, "SW1", "SSSS711403", swx, swy, 0,
        footprint="teacup-carrier:SW-TH_SSSS711403",
        ref_at=(swx, swy + S(4), 0), value_at=(swx, swy + S(6), 0))
ic_pin(SW, swx, swy, 1, "SW_SENSE_1")
ic_pin(SW, swx, swy, 3, GNDF)
ic_pin(SW, swx, swy, 4, "SW_SENSE_4")
# pins 2/5/6 deliberately NC per the confirmed datasheet pinout

vert2("Device:R", "R10", "10k", S(160), S(104), P3V3F, "SW_SENSE_1", "Resistor_SMD:R_0402_1005Metric")
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s.place(SW2, "SW2", "SSSS711403", sw2x, sw2y, 0,
        footprint="teacup-carrier:SW-TH_SSSS711403",
        ref_at=(sw2x, sw2y + S(4), 0), value_at=(sw2x, sw2y + S(6), 0))
ic_pin(SW2, sw2x, sw2y, 1, "EN_SW_BMC")
ic_pin(SW2, sw2x, sw2y, 3, "SW2_POLE")
ic_pin(SW2, sw2x, sw2y, 4, "EN_SW_ALT")
# pins 2/5/6 deliberately NC per the confirmed datasheet pinout

# ============ Provisioning jumper (JP1): gates SW2 until digipot is safe ============
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s.place(SOIC_NOR, "U13", "W25Q32JVSS", n4x, n4y, 0,
        footprint="Package_SO:SOIC-8_5.23x5.23mm_P1.27mm",
        ref_at=(n4x - S(10), n4y - S(10), 0), value_at=(n4x - S(10), n4y - S(8), 0))
ic_pin(SOIC_NOR, n4x, n4y, 1, "NOR_U4_CE")  # ~CS
ic_pin(SOIC_NOR, n4x, n4y, 2, "SFC_IO1")    # DO
ic_pin(SOIC_NOR, n4x, n4y, 3, "SFC_IO2")    # IO2
ic_pin(SOIC_NOR, n4x, n4y, 4, GNDF)         # GND (bottom)
ic_pin(SOIC_NOR, n4x, n4y, 5, "SFC_IO0")    # DI
ic_pin(SOIC_NOR, n4x, n4y, 6, "SFC_CLK")    # CLK
ic_pin(SOIC_NOR, n4x, n4y, 7, "SFC_IO3")    # IO3
ic_pin(SOIC_NOR, n4x, n4y, 8, P3V3F)        # VCC (top)

# ============ Carrier DIP8 NOR socket (U11, recovery/alternate flash) ============
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s.place(DIP, "U11", "DIP-8 Socket", dx, dy, 0,
        footprint="Package_DIP:DIP-8_W7.62mm_Socket",
        ref_at=(dx - S(10), dy - S(10), 0), value_at=(dx - S(10), dy - S(8), 0))
ic_pin(DIP, dx, dy, 1, "NOR_U5_CE")   # ~CS
ic_pin(DIP, dx, dy, 2, "SFC_IO1")     # DO
ic_pin(DIP, dx, dy, 3, "SFC_IO2")     # IO2
ic_pin(DIP, dx, dy, 4, GNDF)          # GND (bottom)
ic_pin(DIP, dx, dy, 5, "SFC_IO0")     # DI
ic_pin(DIP, dx, dy, 6, "SFC_CLK")     # CLK
ic_pin(DIP, dx, dy, 7, "SFC_IO3")     # IO3
ic_pin(DIP, dx, dy, 8, P3V3F)         # VCC (top)

# ============ USB power switch (U12, TPS2053BDR) ============
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    ic_pin(TPS, tx, ty, num, spec)

# ============ GPIO expander (U15, TCA9555PWR) ============
# Frees 9 native ESP32 GPIOs (USB_EN1-3, PG_SW5V/VCORE/SW5V_ALT, SW_SENSE_1/4,
# DCJACK_PRESENT) for the ESP-Hosted SPI link -- all slow status/enable
# signals with no real timing requirement, unlike flash chip-select and the
# power-domain switching GPIOs, which stay native for margin testing.
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s.place(EXP, "U15", "TCA9555PWR", ex, ey, 0,
        footprint="Package_SO:TSSOP-24_4.4x7.8mm_P0.65mm",
        ref_at=(ex - S(16), ey - S(24), 0), value_at=(ex - S(16), ey - S(22), 0))
ic_pin(EXP, ex, ey, 1, "EXP_INT")
ic_pin(EXP, ex, ey, 2, GNDF)     # A1
ic_pin(EXP, ex, ey, 3, GNDF)     # A2
ic_pin(EXP, ex, ey, 4, "USB_EN1")
ic_pin(EXP, ex, ey, 5, "USB_EN2")
ic_pin(EXP, ex, ey, 6, "USB_EN3")
ic_pin(EXP, ex, ey, 7, "PG_SW5V")
ic_pin(EXP, ex, ey, 8, "PG_VCORE")
ic_pin(EXP, ex, ey, 9, "PG_SW5V_ALT")
ic_pin(EXP, ex, ey, 10, "SW_SENSE_1")
ic_pin(EXP, ex, ey, 11, "SW_SENSE_4")
ic_pin(EXP, ex, ey, 12, GNDF)
ic_pin(EXP, ex, ey, 13, "DCJACK_PRESENT")
# pins 14-20 (P11-P17) deliberately NC -- spare I/O for future use
ic_pin(EXP, ex, ey, 21, GNDF)    # A0
ic_pin(EXP, ex, ey, 22, "I2C_PWR_SCL")
ic_pin(EXP, ex, ey, 23, "I2C_PWR_SDA")
ic_pin(EXP, ex, ey, 24, P3V3F)

out = s.render("BMC - ESP32-S3", str(uuid.uuid4()), "/0f27921f-7420-42c8-af54-47a231c1828e", "4", paper="A3")
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
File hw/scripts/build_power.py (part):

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
s.flag("GND", P1(1), "P", "left")            # PGND
pin_net(P1(2), "+5V_SW", "left")             # VIN
pin_net(P1(3), "U1_EN", "left")              # EN
s.flag("GND", P1(4), "P", "left")            # MODE
s.flag("GND", P1(5), "P", "left")            # FSEL
pin_net(P1(6), "PG_VCORE", "left")           # PG (open-drain, R2 pulls up)
pin_net(P1(12), "VCORE_FB", "right")         # FB
s.flag("GND", P1(11), "P", "right")          # GND
pin_net(P1(10), "U1_SS", "right")            # SS/TR
pin_net(P1(9), "U1_VCC", "right")            # VCC
pin_net(P1(8), "U1_SW", "right")             # SW
pin_net(P1(7), "U1_BST", "right")            # BST

# U1 passive islands
py1 = S(48)
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P2 = lambda n: s.pin(U2, u2x, u2y, 0, str(n))

s.flag("GND", P2(1), "P", "left")            # GND
pin_net(P2(2), "U2_SW", "left")              # SW
pin_net(P2(3), "+5V_SW", "left")             # VIN
pin_net(P2(4), "VDDR_FB", "right")           # FB
pin_net(P2(5), "U2_EN", "right")             # EN
pin_net(P2(6), "U2_BST", "right")            # BST

py2 = S(84)
vert2("Device:C", "C6", "10uF", S(20), py2, "+5V_SW", GNDF, "Capacitor_SMD:C_0805_2012Metric")
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P7 = lambda n: s.pin(U2, u7x, u7y, 0, str(n))

s.flag("GND", P7(1), "P", "left")            # GND
pin_net(P7(2), "U7_SW", "left")              # SW
pin_net(P7(3), "+5V_SW", "left")             # VIN
pin_net(P7(4), "P3V3_FB", "right")           # FB
pin_net(P7(5), "U7_EN", "right")             # EN
pin_net(P7(6), "U7_BST", "right")            # BST

py7 = S(120)
vert2("Device:C", "C16", "10uF", S(20), py7, "+5V_SW", GNDF, "Capacitor_SMD:C_0805_2012Metric")
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s.place(DSCH, "D1", "PMEG2010ER", d1x, d1y, 0,
        footprint="Diode_SMD:D_SOD-123W",
        ref_at=(d1x, d1y - S(3), 0), value_at=(d1x, d1y + S(3), 0))
pin_net(s.pin(DSCH, d1x, d1y, 0, "1"), "U5_VIN", "left")     # K
pin_net(s.pin(DSCH, d1x, d1y, 0, "2"), "+5V_BMC", "right")   # A

d2x, d2y = S(108), S(22)
s.place(DSCH, "D2", "PMEG2010ER", d2x, d2y, 0,
        footprint="Diode_SMD:D_SOD-123W",
        ref_at=(d2x, d2y - S(3), 0), value_at=(d2x, d2y + S(3), 0))
pin_net(s.pin(DSCH, d2x, d2y, 0, "1"), "U5_VIN", "left")     # K
pin_net(s.pin(DSCH, d2x, d2y, 0, "2"), "+5V_ALT", "right")   # A

# ============ Always-on 3.3V LDO (U5, AZ1117CH-3.3) ============
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        footprint="Package_TO_SOT_SMD:SOT-223-3_TabPin2",
        extra_props={"Datasheet": "https://lcsc.com/product-detail/C92102.html"},
        ref_at=(u5x, u5y - S(6), 0), value_at=(u5x, u5y - S(4), 0))
pin_net(s.pin(REG, u5x, u5y, 0, "1"), "U5_VIN", "left")
s.flag("GND", s.pin(REG, u5x, u5y, 0, "2"), "P", "down")
pin_net(s.pin(REG, u5x, u5y, 0, "3"), "+3V3_ALWAYS", "right")
vert2("Device:C", "C14", "1uF", S(128), S(16), "U5_VIN", GNDF, "Capacitor_SMD:C_0603_1608Metric")
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# ============ BMC-branch load switch (U4, TPS22990DMLR) ============
# Gates +5V_BMC (the ESP32's own dedicated USB-C, isolated from every
# other source) onto the shared +5V_SW rail. EN_SW_BMC is arbitrated
# between GPIO (SW5V_EN_BMC, through R21), its own pulldown (R20), and
# SW2's throw1 on the bmc sheet (crosses in via this same label) -- one
# throw of the same on-off-on switch that forces the ALT branch (U14) on
# the other throw.
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        ref_at=(u4x, u4y - S(9), 0), value_at=(u4x, u4y + S(9), 0))
P4 = lambda n: s.pin(U4, u4x, u4y, 0, str(n))

pin_net(P4(1), "U4_CT", "left")              # CT
# pin 2 NC -- deliberately unconnected per datasheet
pin_net(P4(3), "+5V_BMC", "left")            # VIN
pin_net(P4(4), "+5V_BMC", "left")            # VBIAS (tied to VIN)
pin_net(P4(5), "EN_SW_BMC", "left")          # ON
s.flag("GND", P4(6), "P", "right")           # GND
pin_net(P4(7), "PG_SW5V", "right")           # PG (open-drain, R4 pulls up)
pin_net(P4(8), "+5V_SW", "right")            # VOUT
pin_net(P4(9), "+5V_SW", "right")            # VOUT
pin_net(P4(10), "+5V_SW", "right")           # VOUT
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# ============ ALT-branch load switch (U14, TPS22990DMLR) ============
# Gates +5V_ALT (the priority-OR'd DC jack / alt USB-C, see io.kicad_sch
# Q1/Q2) onto the same shared +5V_SW rail. EN_SW_ALT is arbitrated the
# same way as EN_SW_BMC (GPIO + pulldown) but is ALSO hard-overridable by
# SW2's throw4 on the bmc sheet, which ties this node to +5V_ALT (SW2's
# pole) when selected -- low-impedance, beats GPIO16's resistor-limited
# drive. Center = neither throw engaged, GPIO has full control.
U14 = "teacup-carrier:TPS22990DMLR"
u14x, u14y = S(210), S(76)
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        ref_at=(u14x, u14y - S(9), 0), value_at=(u14x, u14y + S(9), 0))
P14 = lambda n: s.pin(U14, u14x, u14y, 0, str(n))

pin_net(P14(1), "U14_CT", "left")            # CT
# pin 2 NC -- deliberately unconnected per datasheet
pin_net(P14(3), "+5V_ALT", "left")           # VIN
pin_net(P14(4), "+5V_ALT", "left")           # VBIAS (tied to VIN)
pin_net(P14(5), "EN_SW_ALT", "left")         # ON
s.flag("GND", P14(6), "P", "right")          # GND
pin_net(P14(7), "PG_SW5V_ALT", "right")      # PG (open-drain, R24 pulls up)
pin_net(P14(8), "+5V_SW", "right")           # VOUT (same shared rail as U4)
pin_net(P14(9), "+5V_SW", "right")           # VOUT
pin_net(P14(10), "+5V_SW", "right")          # VOUT
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vert2("Device:R", "R24", "10k", S(210), S(96), P3V3F, "PG_SW5V_ALT", "Resistor_SMD:R_0402_1005Metric")

# ALT-branch EN arbitration -- same topology as the BMC branch, plus SW2's
# hard override on the bmc sheet (crosses in via the EN_SW_ALT label).
vert2("Device:R", "R23", "1k", S(192), S(60), "SW5V_EN_ALT", "EN_SW_ALT", "Resistor_SMD:R_0402_1005Metric")
vert2("Device:R", "R22", "100k", S(201), S(60), "EN_SW_ALT", GNDF, "Resistor_SMD:R_0402_1005Metric")

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P3 = lambda n: s.pin(U3, u3x, u3y, 0, str(n))

s.flag("GND", P3(1), "P", "left")            # HVC/A0
pin_net(P3(2), "I2C_PWR_SCL", "left")        # SCL
pin_net(P3(3), "I2C_PWR_SDA", "left")        # SDA
s.flag("GND", P3(4), "P", "left")            # VSS
s.flag("GND", P3(5), "P", "left")            # P1B
pin_net(P3(6), "VDDR_FB", "left")            # P1W
pin_net(P3(7), "VDDR", "left")               # P1A
pin_net(P3(8), "VCORE", "right")             # P0A
pin_net(P3(9), "VCORE_FB", "right")          # P0W
s.flag("GND", P3(10), "P", "right")          # P0B
s.flag("+3V3", P3(11), "P", "right")         # WP
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
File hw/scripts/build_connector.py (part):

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    # to arrive at the FFC, so they can be routed straight across without
    # having to cross over each other (which is what forces vias). Per
    # explicit user direction, 2026-07-13.
    60: "MIPI0_GPIO", 61: "MIPI0_SCCB_SDA", 62: "MIPI0_SCCB_SCL",
    63: "GND", 64: "MIPI0_CLKP", 65: "MIPI0_CLKN",
    66: "GND", 67: "MIPI0_D1P", 68: "MIPI0_D1N",
    69: "GND", 70: "MIPI0_D0P", 71: "MIPI0_D0N",
    72: "GND",
    # MIPI1: same pattern, same reasoning (matches J8's FFC pin order).
    73: "MIPI1_GPIO", 74: "MIPI1_SCCB_SDA", 75: "MIPI1_SCCB_SCL",
    76: "GND", 77: "MIPI1_CLKP", 78: "MIPI1_CLKN",
    79: "GND", 80: "MIPI1_D1P", 81: "MIPI1_D1N",
    82: "GND", 83: "MIPI1_D0P", 84: "MIPI1_D0N",
    85: "GND",
}
# ESP-Hosted's host-driven reset line -- ties straight to the BMC ESP32-S3's
# own EN/RST pin (HOSTED_RESET on the bmc sheet), not a GPIO. Host side must
# drive it open-drain (only pulls low) so it doesn't fight R8's pull-up.
UNIT2[86] = "HOSTED_RESET"
# 87-96: primary GMAC (RGMII, T-series MAC position -- T31/T40 reduced
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    unit_pin(u3x, u3y, 3, num, spec)

# ============ Unit 4 (pins 145-192): SAR-ADC + general SMB/I2C + plain GPIO ============
# SAR_AUX0 matches the T41 reference board's dedicated ADC_AUX0 pin (old/docs/
# t31zx_teacup_pinuse.csv pin 32) -- a single-channel analog input outside the
# GPIO mux tables on every SoC checked, not a multi-channel SADC. SMB0/SMB1 here
# are the carrier's GENERAL system I2C headers -- kept electrically separate
# from I2C_ID_SDA/SCL (unit 1, pins 23/24, the carrier-ID EEPROM bus), same
# isolation principle already used for VGA/HDMI DDC on the A1 interposer (SS10).
# GPIO0-15 are plain unclaimed superset pins for whatever's left after every
# named peripheral above -- deliberately generic, not tied to a specific SoC
# pin identity, since "remaining plain GPIO" is itself one of the user's
# approved header clusters. Pins 170-192 (23 pins), plus all of units 5-6
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    UNIT4[153 + i] = f"GPIO{i}"
UNIT4[169] = "GND"
# P170-171 claimed for the audio pair (HPOUTL relocated down from unit 2's
# old pin 58, MICLP for J6's mic signal per TeaCup(C)3.3's J10) -- geography
# -first (UNIVERSAL.md SS8: "audio by the codec block"), clustered together
# rather than HPOUTL sitting alone far from MICLP. GND on both sides (169,
# 172) preserves the same "sensitive analog, isolated on both sides" intent
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
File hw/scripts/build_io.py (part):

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s.place(AO3401A, "Q1", "AO3401A", q1x, q1y, 0,
        footprint="Package_TO_SOT_SMD:SOT-23",
        ref_at=(q1x - S(8), q1y - S(3), 0), value_at=(q1x - S(8), q1y + S(3), 0))
q_pin(AO3401A, q1x, q1y, AO_S, "DCJACK_VBUS")
q_pin(AO3401A, q1x, q1y, AO_D, "+5V_ALT")
q_pin(AO3401A, q1x, q1y, AO_G, "Q1_GATE")
vert2("Device:R", "R15", "100k", q1x, S(145), "Q1_GATE", GNDF, "Resistor_SMD:R_0402_1005Metric")

q2x, q2y = S(105), S(130)
s.place(AO3401A, "Q2", "AO3401A", q2x, q2y, 0,
        footprint="Package_TO_SOT_SMD:SOT-23",
        ref_at=(q2x - S(8), q2y - S(3), 0), value_at=(q2x - S(8), q2y + S(3), 0))
q_pin(AO3401A, q2x, q2y, AO_S, "ALTUSB_VBUS")
q_pin(AO3401A, q2x, q2y, AO_D, "+5V_ALT")
q_pin(AO3401A, q2x, q2y, AO_G, "Q2_GATE")
vert2("Device:R", "R16", "4.7k", S(105), S(145), "DCJACK_VBUS", "Q2_GATE", "Resistor_SMD:R_0402_1005Metric")
vert2("Device:R", "R17", "100k", S(114), S(145), "Q2_GATE", GNDF, "Resistor_SMD:R_0402_1005Metric")
# Bulk/bypass cap at the OR'd output node, before +5V_ALT reaches U14
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})

# ============ External amplifier/mic tap (J38) ============
# 3-pin header (HPOUTL, GND, MICLP) tapping the same three audio signals
# J6 carries, in parallel with the jack itself, so an external amplifier
# AND an external mic can both be wired in directly instead of needing a
# breakout cable off J6. GND placed in the middle (rather than at the
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
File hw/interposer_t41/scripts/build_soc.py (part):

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carrier's fixed 288-finger table -- 58 direct matches, 11 pushed to
spares (no matching carrier finger exists for these), 0 conflicts.
Genuine capability difference from T31: T41 has usable MSC1_D0-D3 and
SSI1_DT/DR pins where T31 had to sacrifice those to higher-priority
functions, and T41 has a real dedicated DDR supply rail (VCC_DDR) tied
to J1's VDDR fingers, unlike T31 which folded its DDR domain into
+1V8. Per explicit user direction, 2026-07-19.
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    "16": ("LOCAL", "EXCLK_O"),
    "17": ("RAIL", "+1V8"),
    "18": ("NET", "SPARE_P175"),
    "19": ("NET", "MIPI0_GPIO"),
    "20": ("NET", "SMB0_SDA"),
    "21": ("NET", "SMB0_SCK"),
    "22": ("RAIL", "+1V8"),
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    "76": ("NET", "SPARE_P190"),
    "77": ("NET", "SMB1_SDA"),
    "78": ("NET", "SMB1_SCK"),
    "79": ("NET", "GPIO0"),
    "80": ("NET", "SPARE_P179"),
    "81": ("RAIL", "VCORE"),
    "82": ("RAIL", "VDDR"),
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vert2("Device:C", "C77", "12pF", S(30), S(20), "EXCLK_I", GNDF, "Capacitor_SMD:C_0402_1005Metric")
vert2("Device:C", "C80", "12pF", S(38), S(20), "EXCLK_O_INT", GNDF, "Capacitor_SMD:C_0402_1005Metric")
# R24 (33R series) sits between the crystal's own node (EXCLK_O_INT) and
# the pin's actual EXCLK_O net. R23 (1M feedback) spans the FULL loop --
# EXCLK_I straight to the final EXCLK_O, on the far side of R24 -- not to
# the crystal's own intermediate node. Confirmed against a high-res crop
# of the real schematic: R23's bottom terminal lands on the same node as
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# --- VCM local bypass (matches T31's own audio codec VCM bypass topology). ---
vert2("Device:C", "C69", "4.7uF", S(20), S(45), "VCM", GNDF, "Capacitor_SMD:C_0603_1608Metric")

# --- VCORE decoupling (x8, 100nF/0402, matches T41's 8 VDD pins). ---
for i, ref in enumerate(["C43", "C44", "C45", "C46", "C47", "C48", "C49", "C50"]):
    vert2("Device:C", ref, "100nF", S(20 + i * 6), S(60), "VCORE", GNDF, "Capacitor_SMD:C_0402_1005Metric")

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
